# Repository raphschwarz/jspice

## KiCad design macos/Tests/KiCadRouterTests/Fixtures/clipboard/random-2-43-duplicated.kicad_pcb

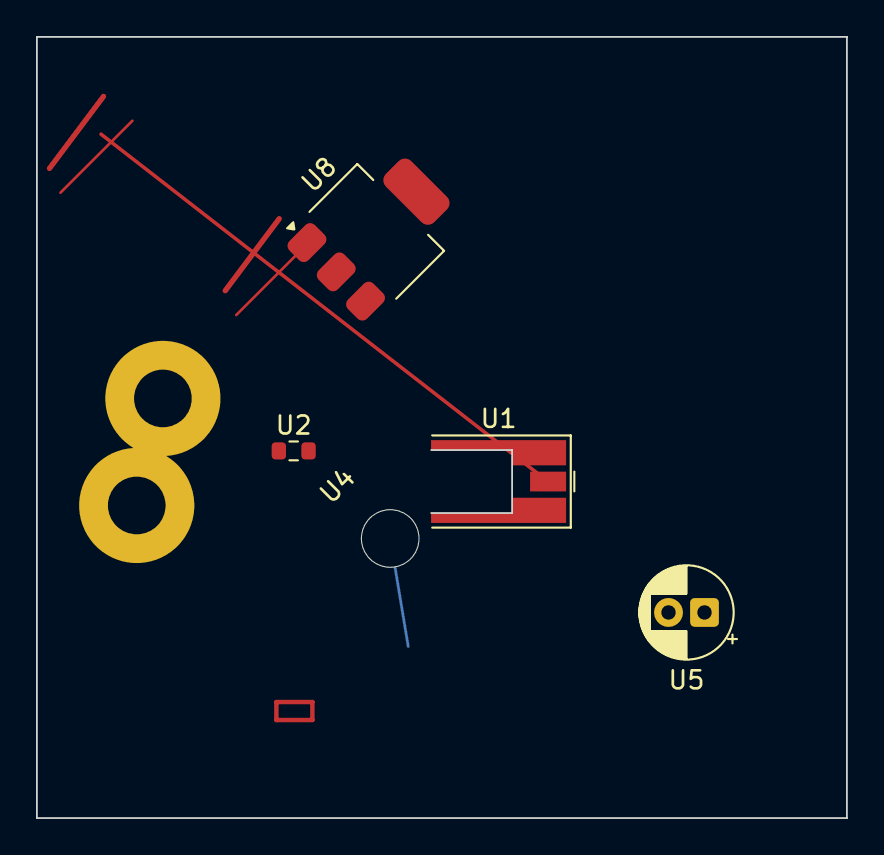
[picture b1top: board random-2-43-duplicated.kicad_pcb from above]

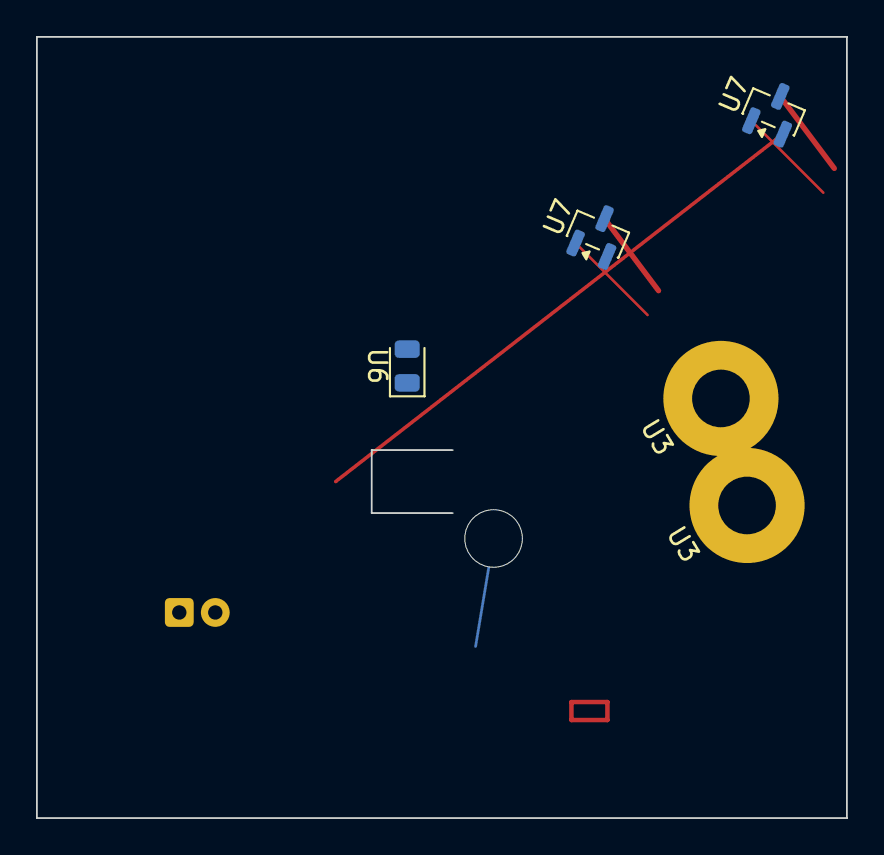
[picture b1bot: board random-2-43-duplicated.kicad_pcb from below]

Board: 4 copper layers, 45.0 x 43.4 mm, 10 parts (5 on the bottom side), 3 nets.

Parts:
U1: MMCX_Molex_73415-0961_Horizontal_0.8mm-PCB
U2: R_0603_1608Metric
U3, U3#2: MountingHole_3.2mm_M3_Pad
U4: MountingHole_3.2mm_M3
U5: CP_Radial_D5.0mm_P2.00mm
U6: LED_0805_2012Metric
U7, U7#2: SOT-23
U8: SOT-223-3_TabPin2

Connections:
D12: U6.1, U7.2, U7#2.2
N1: U3.1, U3#2.1, U6.2
N3: U2.2, U7.3, U7#2.3, U8.3

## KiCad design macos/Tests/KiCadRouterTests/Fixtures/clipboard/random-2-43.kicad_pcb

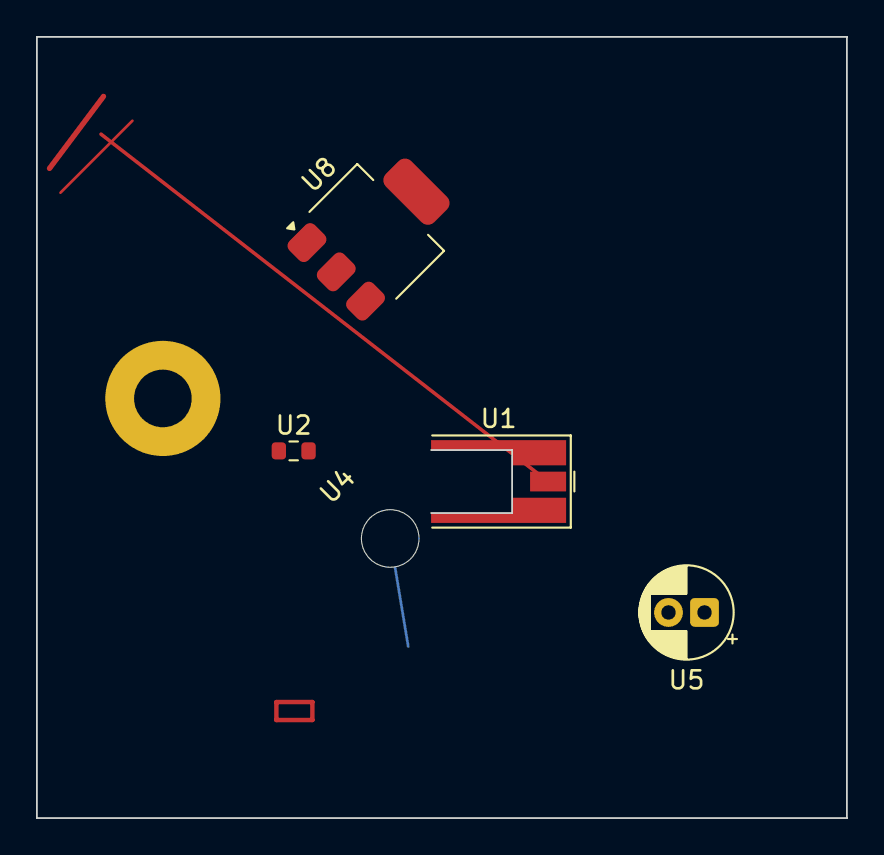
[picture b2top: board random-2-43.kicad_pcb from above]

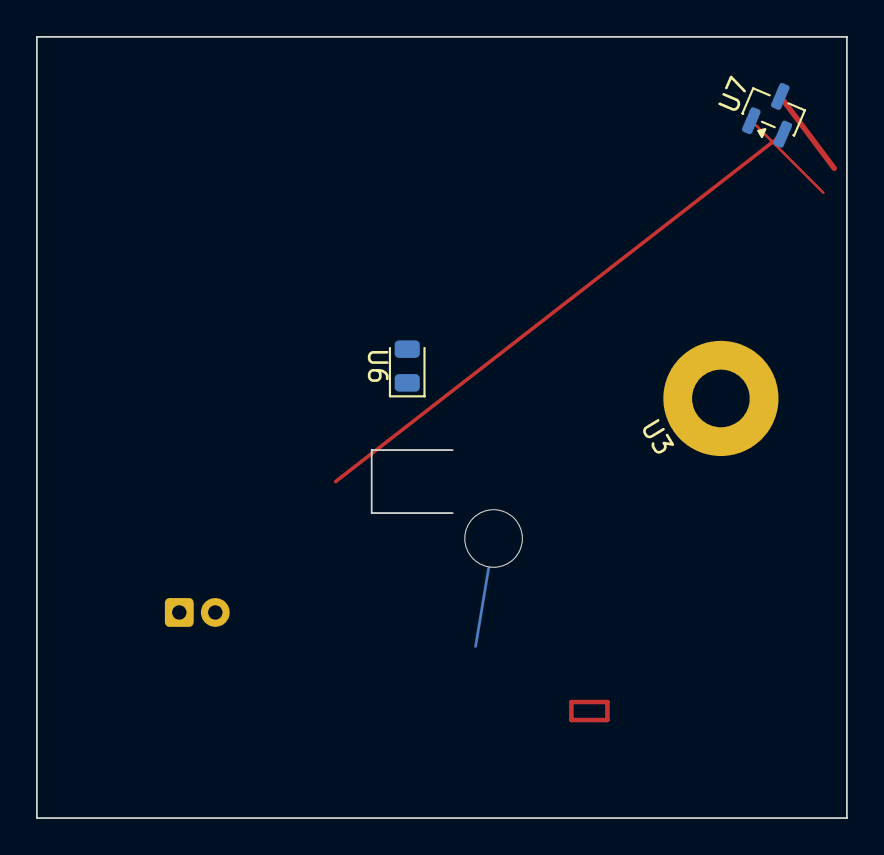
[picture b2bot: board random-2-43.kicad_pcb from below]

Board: 4 copper layers, 45.0 x 43.4 mm, 8 parts (3 on the bottom side), 3 nets.

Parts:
U1: MMCX_Molex_73415-0961_Horizontal_0.8mm-PCB
U2: R_0603_1608Metric
U3: MountingHole_3.2mm_M3_Pad
U4: MountingHole_3.2mm_M3
U5: CP_Radial_D5.0mm_P2.00mm
U6: LED_0805_2012Metric
U7: SOT-23
U8: SOT-223-3_TabPin2

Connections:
D12: U6.1, U7.2
N1: U3.1, U6.2
N3: U2.2, U7.3, U8.3

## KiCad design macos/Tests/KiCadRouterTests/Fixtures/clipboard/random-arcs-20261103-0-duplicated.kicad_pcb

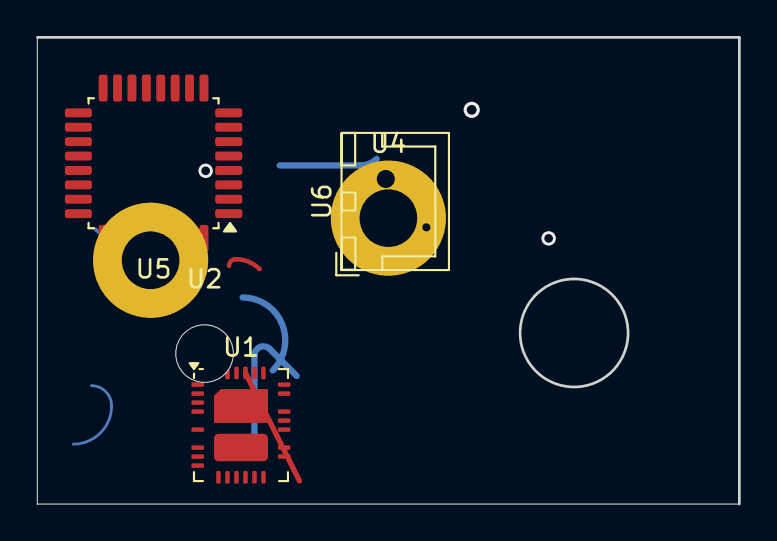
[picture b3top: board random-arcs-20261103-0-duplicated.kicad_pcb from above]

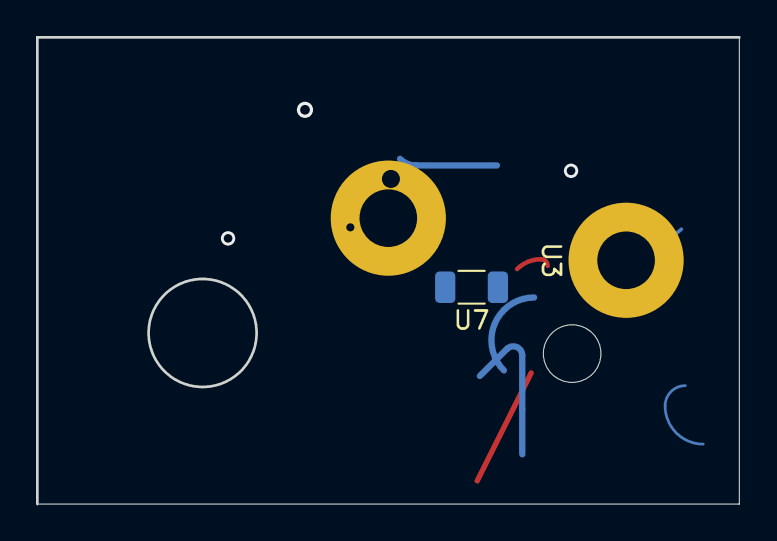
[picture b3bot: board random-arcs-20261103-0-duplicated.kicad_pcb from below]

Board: 2 copper layers, 39.0 x 25.9 mm, 7 parts (2 on the bottom side), 9 nets.

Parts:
U1: Analog_QFN-28-36-2EP_5x6mm_P0.5mm
U2: MountingHole_3.2mm_M3
U3, U4: MountingHole_3.2mm_M3_Pad
U5: LQFP-32_7x7mm_P0.8mm
U6: JST_XH_B2B-XH-A_1x02_P2.50mm_Vertical
U7: R_1206_3216Metric

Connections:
/sub/clk: U1.1, U1.14, U1.27, U5.1, U5.14, U5.18, U5.30
D7: U1.20, U1.24, U5.3, U5.11, U5.20
D12: U1.9, U5.21, U5.25
GND: U1.6, U1.21, U4.1, U5.2, U5.6
N1: U1.2, U1.10, U1.16, U1.36, U5.9, U5.13, U5.17, U5.19, U5.31, U6.1
N2: U1.37, U3.1, U5.12, U5.32, U7.2
N3: U1.33, U5.4, U5.10
PWR1: U1.17, U1.25, U1.28, U1.38, U5.8, U5.27, U5.29
SIG2: U1.13, U5.26, U7.1
